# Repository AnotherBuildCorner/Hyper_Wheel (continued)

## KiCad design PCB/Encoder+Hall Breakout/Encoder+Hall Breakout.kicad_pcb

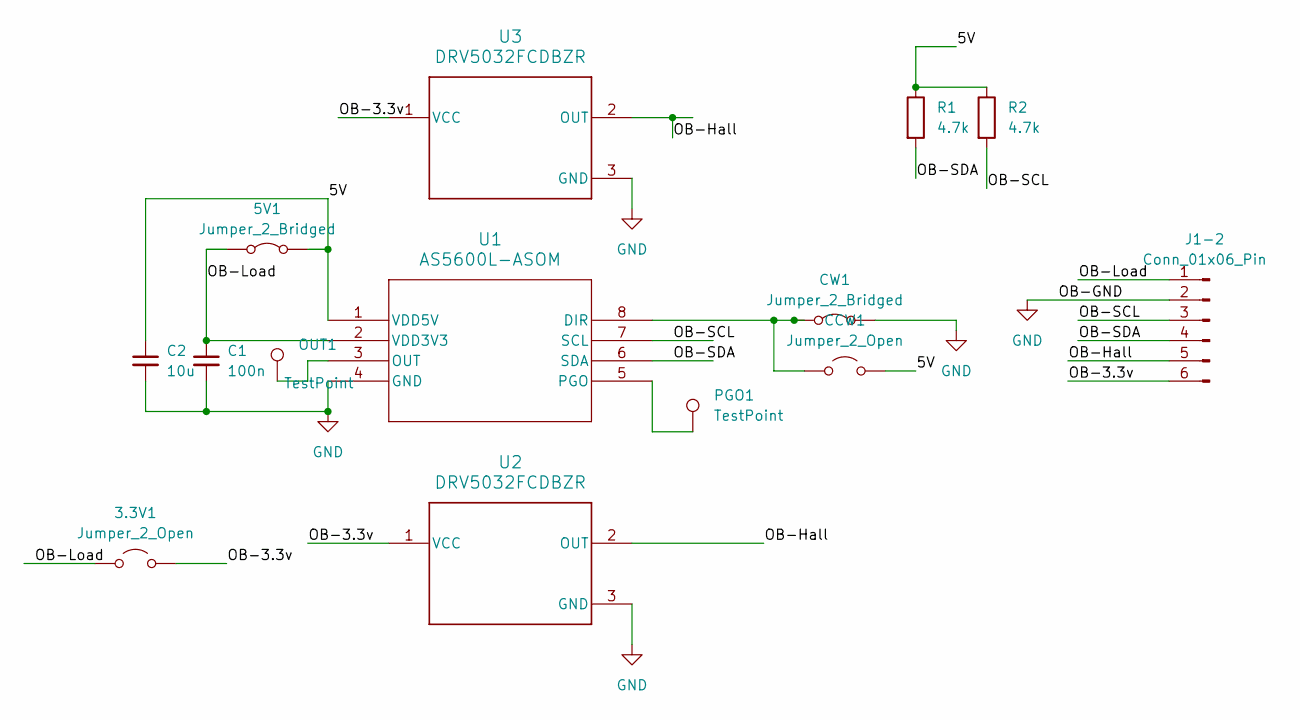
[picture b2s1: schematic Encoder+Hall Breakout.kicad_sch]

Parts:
3.3V1: Jumper_2_Open; SolderJumper-2_P1.3mm_Open_Pad1.0x1.5mm
5V1: Jumper_2_Bridged; SolderJumper-2_P1.3mm_Bridged_Pad1.0x1.5mm
C1: 100n; C_0603_1608Metric_Pad1.08x0.95mm_HandSolder
C2: 10u; C_0603_1608Metric_Pad1.08x0.95mm_HandSolder
CCW1: Jumper_2_Open; SolderJumper-2_P1.3mm_Open_Pad1.0x1.5mm
CW1: Jumper_2_Bridged; SolderJumper-2_P1.3mm_Bridged_Pad1.0x1.5mm
J1-2: Conn_01x06_Pin; PinHeader_1x06_P2.54mm_Vertical
OUT1: TestPoint; PinHeader_1x01_P1.00mm_Vertical
PGO1: TestPoint; TestPoint_Pad_D2.0mm
R1, R2: 4.7k; R_0603_1608Metric_Pad0.98x0.95mm_HandSolder
U1: AS5600L-ASOM; AS5600L-ASOM_AMS
U2, U3: DRV5032FCDBZR; DRV5032-DBZ0003A-MFG

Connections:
/5V: 5V1.2 (B), C2.1, CCW1.2 (B), R1.1, R2.1, U1.1 (VDD5V)
/OB-3.3v: 3.3V1.2 (B), J1-2.6, U2.1 (VCC), U3.1 (VCC)
/OB-Hall: J1-2.5, U2.2 (OUT), U3.2 (OUT)
/OB-Load: 3.3V1.1 (A), 5V1.1 (A), C1.1, J1-2.1, U1.2 (VDD3V3)
/OB-SCL: J1-2.3, R2.2, U1.7 (SCL)
/OB-SDA: J1-2.4, R1.2, U1.6 (SDA)
GND: C1.2, C2.2, CW1.2 (B), J1-2.2, U1.4 (GND), U2.3 (GND), U3.3 (GND)
unnamed: CCW1.1 (A), CW1.1 (A), U1.8 (DIR)
unnamed: OUT1.1 (1_1), U1.3 (OUT)
unnamed: PGO1.1 (1_1), U1.5 (PGO)

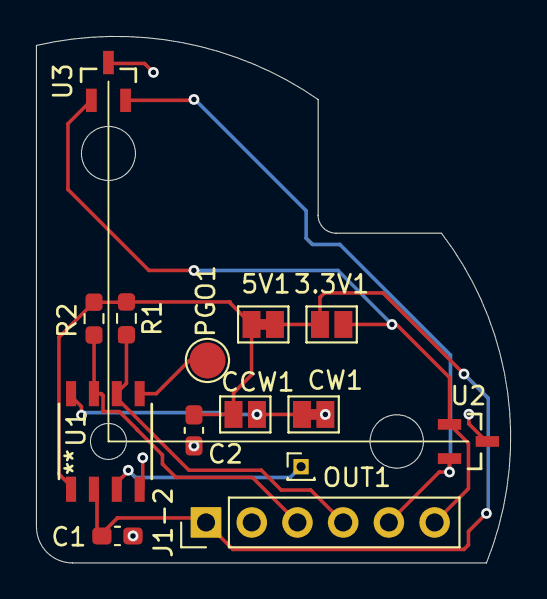
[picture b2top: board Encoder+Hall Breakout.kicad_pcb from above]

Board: 2 copper layers, 26.3 x 29.2 mm, 14 parts (0 on the bottom side), 10 nets.

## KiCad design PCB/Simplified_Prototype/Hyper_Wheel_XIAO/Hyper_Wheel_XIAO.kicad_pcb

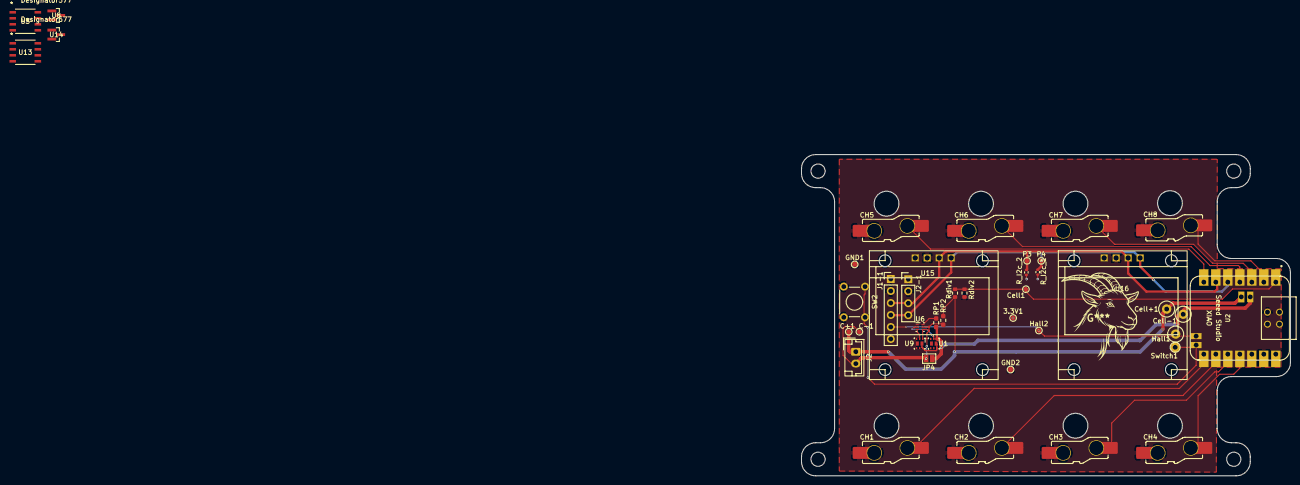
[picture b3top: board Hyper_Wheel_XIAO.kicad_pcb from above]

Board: 2 copper layers, 103.5 x 68.0 mm, 43 parts (0 on the bottom side), 26 nets.

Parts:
3.3V1: TestPad; TestPoint_Pad_D1.0mm
C+1: TestPad; TestPoint_Pad_D1.0mm
C-1: TestPad; TestPoint_Pad_D1.0mm
CH1, CH2, CH3, CH4, CH5, CH6, CH7, CH8: KS33_SW_HS; SW_KS33_HS_KS-2P02B01-02_HS_1u
CP1: 0.1u; C_0201_0603Metric_Pad0.64x0.40mm_HandSolder
Cell1: TestPad; TestPoint_Pad_D1.0mm
Cell+1: TestPoint; TestPoint_Plated_Hole_D2.0mm
Cell-1: TestPoint; TestPoint_Plated_Hole_D2.0mm
GND1, GND2: TestPad; TestPoint_Pad_D1.0mm
Hall1: TestPoint; TestPoint_Plated_Hole_D2.0mm
Hall2: TestPad; TestPoint_Pad_D1.0mm
J1-1: Conn_01x06_Socket; PinHeader_1x06_P2.54mm_Vertical
J2: LIPO; JST_EH_B2B-EH-A_1x02_P2.50mm_Vertical
J2-1: Conn_01x04_Socket; PinHeader_1x04_P2.54mm_Vertical
JP4: Jumper_2_Bridged; SolderJumper-2_P1.3mm_Open_Pad1.0x1.5mm
P3, P4: TestPad; TestPoint_Pad_D1.0mm
RP1: 2.2k; R_0603_1608Metric_Pad0.98x0.95mm_HandSolder
RP2: 330; R_0603_1608Metric_Pad0.98x0.95mm_HandSolder
R_I2c_1, R_I2c_2: 4.7k; R_0402_1005Metric
Rdiv1: 150k; R_0603_1608Metric
Rdiv2: 300k; R_0603_1608Metric
SW2: SW_Push; SW_TH_Tactile_Omron_B3F-100x
Switch1: TestPoint; TestPoint_Plated_Hole_D2.0mm
U1, U9: CSD85301Q2; CDS85301-DQK0006B
U2: Seeed Studio XIAO nRF52840; XIAO-nRF52840-Sense-14P-THTMOD
U3, U13: AS5600L-ASOM; AS5600L-ASOM_AMS
U6: BQ29700DSER; BQ29700-DSE0006A
U8, U14: DRV5032FCDBZR; DRV5032-DBZ0003A-IPC_A
U15, U16: OLED 128x64

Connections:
3.3V_Regulated: 3.3V1.1 (Pin_1_1), J1-1.1, J1-1.6, J2-1.1, R_I2c_1.1, R_I2c_2.1, U2.12 (3V3), U15.1 (VCC), U16.1 (VCC)
/Cell-: Cell-1.1 (1_1), JP4.2 (B), RP1.2, U1.1 (S1), U2.21 (BAT-)
/Cell_monitor: Cell1.1 (Pin_1_1), Rdiv1.2, Rdiv2.1, U2.1 (P0.02_A0_D0)
/Hall_1: Hall1.1 (1_1), Hall2.1 (Pin_1_1), J1-1.5, U2.19 (P0.09_NFC1)
/I2C_1_SCL: J1-1.3, J2-1.3, P3.1 (Pin_1_1), R_I2c_2.2, U2.6 (P0.05_A5_D5_SCL), U15.3 (SCL), U16.3 (SCL)
/I2C_1_SDA: J1-1.4, J2-1.4, P4.1 (Pin_1_1), R_I2c_1.2, U2.5 (P0.04_A4_D4_SDA), U15.4 (SDA), U16.4 (SDA)
/Key1: CH1.1, U2.8 (P1.12_D7_RX)
/Key2: CH2.1, U2.9 (P1.13_D8_SCK)
/Key3: CH3.1, U2.10 (P1.14_D9_MISO)
/Key4: CH4.1, U2.11 (P1.15_D10_MOSI)
/Key5: CH5.1, U2.7 (P1.11_D6_TX)
/Key6: CH6.1, U2.4 (P0.29_A3_D3)
/Key7: CH7.1, U2.3 (P0.28_A2_D2)
/Key8: CH8.1, U2.2 (P0.03_A1_D1)
/Peripherals/OB-3.3v: U8.1 (VCC), U14.1 (VCC)
/Peripherals/OB-GND: U3.4 (GND), U8.3 (GND), U14.3 (GND)
/Peripherals/OB-Hall: U8.2 (OUT), U14.2 (OUT)
/Power Handling/Cell-: C-1.1 (Pin_1_1), CP1.2, J2.2, JP4.1 (A), U6.4 (VSS), U9.1 (S1)
/Switch: SW2.1, Switch1.1 (1_1), U2.20 (P0.10_NFC2)
ChargerOUT: C+1.1 (Pin_1_1), Cell+1.1 (1_1), J2.1, RP2.2, Rdiv1.1, U2.22 (BAT+)
GND: CH1.2, CH2.2, CH3.2, CH4.2, CH5.2, CH6.2, CH7.2, CH8.2, GND1.1 (Pin_1_1), GND2.1 (Pin_1_1), J1-1.2, J2-1.2, Rdiv2.2, SW2.2, U2.13 (GND), U2.17 (GND), U15.2 (GND), U16.2 (GND)
unnamed: U1.6 (D1), U1.7 (D1), U9.6 (D1), U9.7 (D1)
unnamed: U1.2 (G1), U6.2 (COUT)
unnamed: CP1.1, RP2.1, U6.5 (BAT)
unnamed: U6.3 (DOUT), U9.2 (G1)
unnamed: RP1.1, U6.6 (V-)

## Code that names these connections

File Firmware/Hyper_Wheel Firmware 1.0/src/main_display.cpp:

#include "main_display.h"

#include "action_layer.h"

#include <Arduino.h>
#include <Wire.h>
#include <Adafruit_GFX.h>
#include <Adafruit_SSD1306.h>
#include <string.h>

static constexpr uint8_t SCREEN_WIDTH = 128;
static constexpr uint8_t SCREEN_HEIGHT = 64;
static constexpr int OLED_RESET = -1;
static constexpr uint8_t OLED_ADDR_A = 0x3D;
static constexpr uint8_t OLED_ADDR_B = 0x3C;

static Adafruit_SSD1306 displayA(SCREEN_WIDTH, SCREEN_HEIGHT, &Wire, OLED_RESET);
static Adafruit_SSD1306 displayB(SCREEN_WIDTH, SCREEN_HEIGHT, &Wire, OLED_RESET);

static DisplayState gLastRenderedNormalState{};
static bool gHasRenderedNormalOnce = false;

static uint8_t gLastRenderedMenuMode = 255;
static uint8_t gLastRenderedHighlight = 255;
static bool gHasRenderedMenuOnce = false;

static bool displayStateEquals(const DisplayState& a, const DisplayState& b) {
    return memcmp(&a, &b, sizeof(DisplayState)) == 0;
}

static void copyLabel(char dest[DISPLAY_LABEL_LEN + 1], const char* src) {
    strncpy(dest, src, DISPLAY_LABEL_LEN);
    dest[DISPLAY_LABEL_LEN] = '\0';
}

void displaySetProfileName(DisplayState& state, const char* text) {
    copyLabel(state.profileName, text);
}

void displaySetLastCommand(DisplayState& state, const char* text) {
    copyLabel(state.lastCommand, text);
}

void displayFillFromKeyLabels(DisplayState& state,
                              const char keyLabels[8][DISPLAY_LABEL_LEN + 1]) {
    copyLabel(state.screenA[0], keyLabels[4]); // Key5
    copyLabel(state.screenA[1], keyLabels[5]); // Key6
    copyLabel(state.screenA[2], keyLabels[0]); // Key1
    copyLabel(state.screenA[3], keyLabels[1]); // Key2

    copyLabel(state.screenB[0], keyLabels[6]); // Key7
    copyLabel(state.screenB[1], keyLabels[7]); // Key8
    copyLabel(state.screenB[2], keyLabels[2]); // Key3
    copyLabel(state.screenB[3], keyLabels[3]); // Key4
}

static void drawQuadrants(Adafruit_SSD1306& d,
                          const char labels[4][DISPLAY_LABEL_LEN + 1],
                          const char* centerText) {
    d.clearDisplay();
    d.setTextColor(SSD1306_WHITE);

    d.setTextSize(1);
    d.setCursor(0, 0);
    d.print(labels[0]);

    d.setCursor(74, 0);
    d.print(labels[1]);

    d.setCursor(0, 54);
    d.print(labels[2]);

    d.setCursor(74, 54);
    d.print(labels[3]);

    d.setTextSize(2);

    int16_t x1, y1;
    uint16_t w, h;
    d.getTextBounds(centerText, 0, 0, &x1, &y1, &w, &h);

    int16_t cx = (SCREEN_WIDTH - w) / 2;
    int16_t cy = (SCREEN_HEIGHT - h) / 2;

    d.setCursor(cx, cy);
    d.print(centerText);

    d.display();
}

static void drawPresetPickerScreenA(Adafruit_SSD1306& d,
                                    uint8_t highlightedPreset,
                                    uint8_t profileCount) {
    d.clearDisplay();
    d.setTextColor(SSD1306_WHITE);

    d.setTextSize(2);
    d.setCursor(0, 0);
    d.print("PRESET");

    d.setTextSize(1);
    d.setCursor(0, 24);
    d.print("Turn: Browse");

    d.setCursor(0, 36);
    d.print("Sys: Select");

    d.setCursor(0, 54);
    d.print(highlightedPreset + 1);
    d.print("/");
    d.print(profileCount);

    d.display();
}

static void drawPresetPickerScreenB(Adafruit_SSD1306& d,
                                    const ActionLayerState& actionState) {
    d.clearDisplay();
    d.setTextColor(SSD1306_WHITE);
    d.setTextSize(1);

    const char* prev = actionLayerGetMenuItemLabel(actionState, 0);
    const char* curr = actionLayerGetMenuItemLabel(actionState, 1);
    const char* next = actionLayerGetMenuItemLabel(actionState, 2);

    uint8_t item = actionState.highlightedPreset;

    d.setCursor(0, 8);
    d.print(" ");
    if (item > 0) {
        d.print(item);
        d.print(": ");
    } else {
        d.print("   ");
    }
    d.print(prev);

    d.drawRect(0, 24, SCREEN_WIDTH, 16, SSD1306_WHITE);
    d.setCursor(2, 28);
    d.print(">");
    d.print(item + 1);
    d.print(": ");
    d.print(curr);

    d.setCursor(0, 48);
    d.print(" ");
    if ((item + 1) < actionState.config->profileCount) {
        d.print(item + 2);
        d.print(": ");
    } else {
        d.print("   ");
    }
    d.print(next);

    d.display();
}

bool displayBegin() {
    Wire.begin();

    if (!displayA.begin(SSD1306_SWITCHCAPVCC, OLED_ADDR_A)) {
        return false;
    }

    if (!displayB.begin(SSD1306_SWITCHCAPVCC, OLED_ADDR_B)) {
        return false;
    }

    displayA.clearDisplay();
    displayA.display();

    displayB.clearDisplay();
    displayB.display();

    return true;
}

void displayRenderNormal(const DisplayState& state) {
    if (gHasRenderedNormalOnce && displayStateEquals(state, gLastRenderedNormalState)) {return;}

    drawQuadrants(displayA, state.screenA, state.profileName);
    drawQuadrants(displayB, state.screenB, state.lastCommand);

    memcpy(&gLastRenderedNormalState, &state, sizeof(DisplayState));
    gHasRenderedNormalOnce = true;
    gHasRenderedMenuOnce = false;
}

void displayRenderPresetPicker(const ActionLayerState& actionState) {
    if (actionState.config == nullptr || actionState.config->profileCount == 0) {
        return;
    }

    if (gHasRenderedMenuOnce &&
        gLastRenderedMenuMode == static_cast<uint8_t>(actionState.mode) &&
        gLastRenderedHighlight == actionState.highlightedPreset) {
        return;
    }

    drawPresetPickerScreenA(displayA,
                            actionState.highlightedPreset,
                            actionState.config->profileCount);

    drawPresetPickerScreenB(displayB, actionState);

    gLastRenderedMenuMode = static_cast<uint8_t>(actionState.mode);
    gLastRenderedHighlight = actionState.highlightedPreset;
    gHasRenderedMenuOnce = true;
}

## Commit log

2026-03-25 stage 1- power system wiring
2026-04-03 Base Push
2026-04-03 Missing TVS Diode places
2026-04-06 Updated work on antenna, And adjusted log structure
2026-04-06 4-6 progress update
2026-04-07 Main board nearing RevA completion
2026-04-07 split out magnetic encoder on "ribbon cables" reduces board size
2026-04-10 power plane added, passes Peer review
2026-04-10 Added test pads,
2026-04-11 simulation headaches
2026-04-13 XIAO based test board complete
2026-04-13 log updates
2026-04-13 Encoder Breakout added
2026-04-13 fabrication submit for XIAO and encoder wheels
2026-04-13 Final cleanup
2026-04-13 added Revision mark
2026-04-13 Added entry to log. Production Hold now.
2026-04-14 Readme Update
2026-04-14 Photo Link Fix
2026-04-14 try 2
2026-04-14 try 3
2026-04-14 Repaired Broken image links
2026-04-14 Cleanup
2026-04-14 update progress log
2026-04-14 folder rename
2026-04-14 added Power budget
2026-04-15 Readme Rewrite
2026-04-15 readme edits
2026-04-15 duplicate metal 2's
2026-04-15 Update prep
2026-04-15 Switched Load switch update
2026-04-15 revA-1 gerbers
2026-04-17 Firmware Begin, Encoder and button core online
2026-04-17 Main display and BLE roots
2026-04-17 progress update
2026-04-19 working on abstraction layers
2026-04-20 Encoder profiles added, keymap moved
2026-04-20 begin memory implementation, compressed some files
2026-04-20 begin preset menu implementation.
2026-04-20 sticky menu fix and main preset edit
2026-04-20 keymap shift. Odd.
2026-04-20 progress entries
2026-04-25 Rev B Xiao. migrated changes to main
2026-04-26 added .5mm pitch ribbon cable. install TBD
2026-04-27 RevB Xiao Updates. Fab
2026-04-29 REV_B Xiao
2026-05-09 begin dual encoder migration
2026-05-09 Dual Encoder migration complete. not enabled
2026-05-09 added a tiny cell voltage monitor. more work required
